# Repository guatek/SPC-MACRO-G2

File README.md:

# KiCAD Electronics for Gen 2 SPC-MACRO with Fluorescence Imaging

## Overview

This design is based on the first generation of the SPC-MACRO that used a system controller from the OriginalDesign/SPC-UW-MOD1 project and illumination from the OriginalDesign/SPCInterfaceBoard-SPCPWSSC/SPCInterfaceBoard-v01.kicad_pro project. The system control and power path are standard items that are in general common to most SPC microscopes. In contrast, the illumination is specific to the SPC-MACRO.

## Generation 2 changes

The G2 version is targeting fluorescence imaging and as such replaces the color darkfield ring illumination with Cree XE-G Violet ring illumination on both sides of the imaged volume. The system retains the small-angle color darkfield illumination used in the SPC-MACRO.

## Actions Items 

- Update the existing projects (SPCInterfaceBoard-v01.kicad_pro, and SPC-UW-MOD1.kicad_pcb) to work with KiCAD 7 (this is mostly done).
- Consolidate the upgrades from recent dual-mag projects and existing SPC-MACRO project to a single controller using either the SAMD21 or SAMD51. Functions of the dual-mag and SPC-MACRO should be retained. 
- Review and revise the illumination electronics and updated as needed to bring into parity with the latest dual-mag illumination.
- Update system controller and color darkfield illumination layout to fit in 4" ID form factor so boards can be used with dual-mag cameras.
- Add darkfield ring illumination with XE-G Violet LEDs packed as close as possible with Ledil 10 mm secondary optics.

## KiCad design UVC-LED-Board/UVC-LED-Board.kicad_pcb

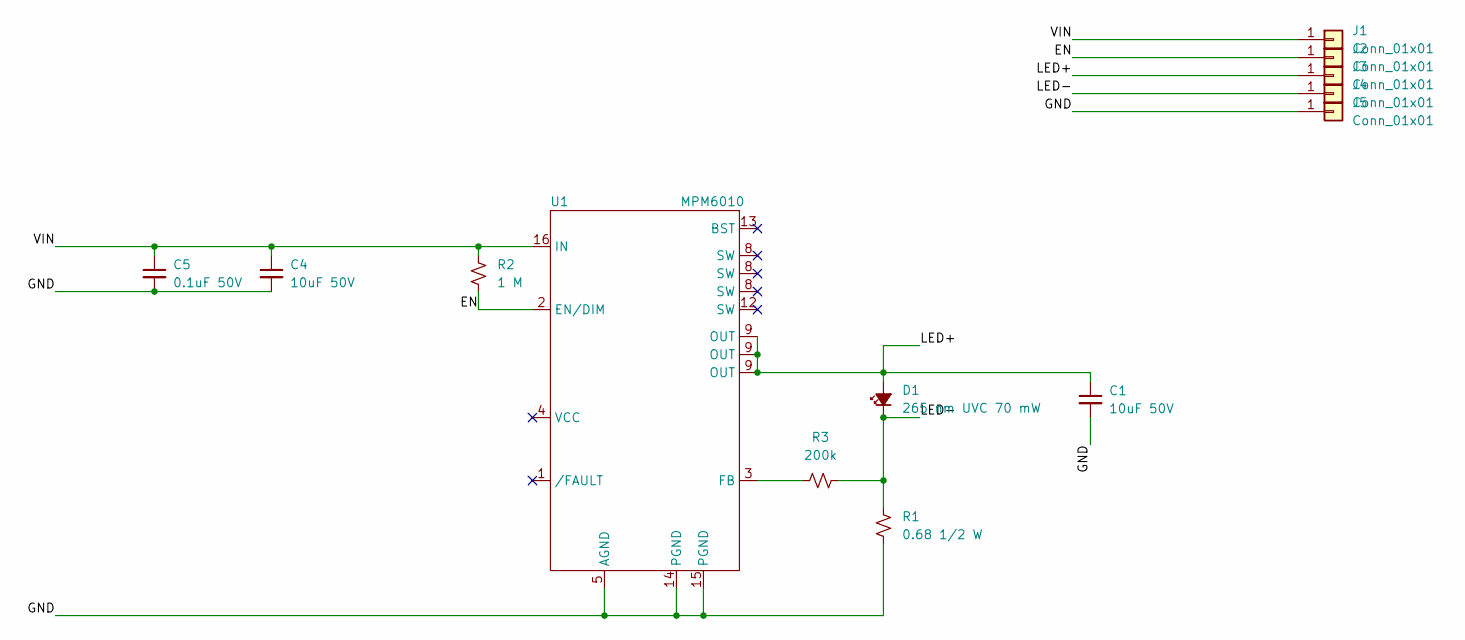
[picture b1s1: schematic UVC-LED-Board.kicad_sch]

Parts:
C1, C4: 10uF 50V; C_0805_2012Metric; Part Number 2571-GMC21X5R106K50NTTR-ND
C5: 0.1uF 50V; C_0402_1005Metric; Part Number 490-14514-1-ND
D1: 265 nm UVC 70 mW; ZEUBE265-1DA
J1, J2, J3, J4, J5: Conn_01x01; One_PTH
R1: 0.68 1/2 W; R_0805_2012Metric; Part Number P19304CT-ND
R2: 1 M; R_0402_1005Metric; Part Number P1.00MLCT-ND
R3: 200k; R_0402_1005Metric; Part Number P200KLCT-ND
U1: MPM6010; Part Number 1589-1774-1-ND

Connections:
/EN: J2.1, R2.2, U1.2 (EN/DIM)
/GND: C1.2, C4.2, C5.2, J5.1, R1.2, U1.5 (AGND), U1.14 (PGND), U1.15 (PGND)
/LED+: C1.1, D1.2 (A), J3.1, U1.9 (OUT)
/LED-: D1.1 (K), J4.1, R1.1, R3.2
/VIN: C4.1, C5.1, J1.1, R2.1, U1.16 (IN)
unnamed: R3.1, U1.3 (FB)

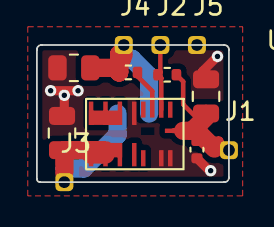
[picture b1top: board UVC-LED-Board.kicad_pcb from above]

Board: 4 copper layers, 10.7 x 7.6 mm, 13 parts (1 on the bottom side), 6 nets.

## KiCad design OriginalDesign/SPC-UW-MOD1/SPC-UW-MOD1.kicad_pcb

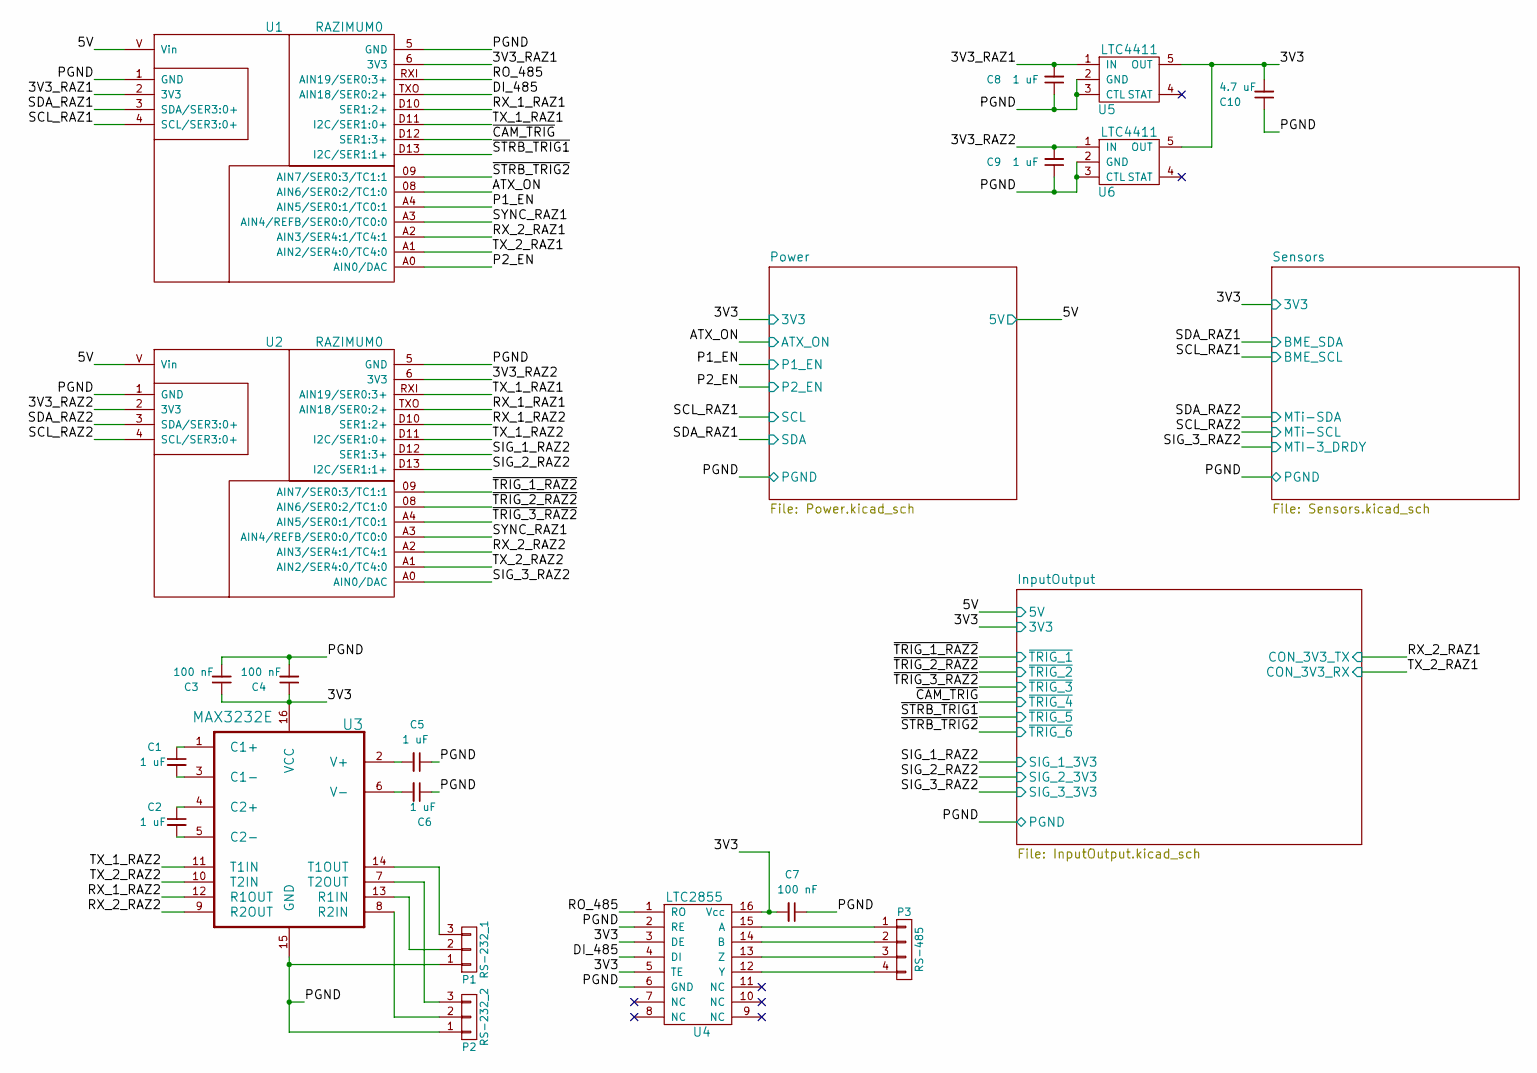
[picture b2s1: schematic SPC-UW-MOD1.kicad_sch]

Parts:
C1, C2, C5, C6: 1 uF; C_0805; Part Number UMK212B7105KG-T
C3, C4, C7: 100 nF; C_0603; Part Number GRM188R71H104KA93D
C8, C9: 1 uF; C_0603; Part Number C1608X7R1A105K080AC
C10: 4.7 uF; C_0805; Part Number GRM21BR71A475KA73K
P1: RS-232_1; Molex_NanoFit_2x02x2.50mm_Angled
P2: RS-232_2; Molex_NanoFit_2x02x2.50mm_Angled
P3: RS-485; Molex_NanoFit_2x02x2.50mm_Angled
U1, U2: RAZIMUM0
U3: MAX3232E; TSSOP-16_4.4x5mm_Pitch0.65mm; Part Number MAX3232ECUE+T
U4: LTC2855; SSOP-16_3.9x4.9mm_Pitch0.635mm; Part Number LTC2855IGN#PBF
U5, U6: LTC4411; TSOT-23-5

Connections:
/3V3_RAZ1: C8.2, U1.2 (3V3), U1.6 (3V3), U5.1 (IN)
/3V3_RAZ2: C9.2, U2.2 (3V3), U2.6 (3V3), U6.1 (IN)
/5V: U1.V (Vin), U2.V (Vin); also elsewhere on the board
/ATX_ON: U1.08 (AIN6/SER0:2/TC1:0); also elsewhere on the board
/DI_485: U1.TXO (AIN18/SER0:2+), U4.4 (DI)
/P1_EN: U1.A4 (AIN5/SER0:1/TC0:1); also elsewhere on the board
/P2_EN: U1.A0 (AIN0/DAC); also elsewhere on the board
/PGND: C3.2, C4.2, C5.1, C6.1, C7.1, C8.1, C9.1, C10.1, P1.1, P2.1, U1.1 (GND), U1.5 (GND), U2.1 (GND), U2.5 (GND), U3.15 (GND), U4.2 (RE), U4.6 (GND), U5.2 (GND), U5.3 (CTL), U6.2 (GND), U6.3 (CTL); also elsewhere on the board
/RO_485: U1.RXI (AIN19/SER0:3+), U4.1 (RO)
/RX_1_RAZ1: U1.D10 (SER1:2+), U2.TXO (AIN18/SER0:2+)
/RX_1_RAZ2: U2.D10 (SER1:2+), U3.12 (R1OUT)
/RX_2_RAZ1: U1.A2 (AIN3/SER4:1/TC4:1); also elsewhere on the board
/RX_2_RAZ2: U2.A2 (AIN3/SER4:1/TC4:1), U3.9 (R2OUT)
/SCL_RAZ1: U1.4 (SCL/SER3:0+); also elsewhere on the board
/SCL_RAZ2: U2.4 (SCL/SER3:0+); also elsewhere on the board
/SDA_RAZ1: U1.3 (SDA/SER3:0+); also elsewhere on the board
/SDA_RAZ2: U2.3 (SDA/SER3:0+); also elsewhere on the board
/SIG_1_RAZ2: U2.D12 (SER1:3+); also elsewhere on the board
/SIG_2_RAZ2: U2.D13 (I2C/SER1:1+); also elsewhere on the board
/SIG_3_RAZ2: U2.A0 (AIN0/DAC); also elsewhere on the board
/SYNC_RAZ1: U1.A3 (AIN4/REFB/SER0:0/TC0:0), U2.A3 (AIN4/REFB/SER0:0/TC0:0)
/TX_1_RAZ1: U1.D11 (I2C/SER1:0+), U2.RXI (AIN19/SER0:3+)
/TX_1_RAZ2: U2.D11 (I2C/SER1:0+), U3.11 (T1IN)
/TX_2_RAZ1: U1.A1 (AIN2/SER4:0/TC4:0); also elsewhere on the board
/TX_2_RAZ2: U2.A1 (AIN2/SER4:0/TC4:0), U3.10 (T2IN)
/~CAM_TRIG: U1.D12 (SER1:3+); also elsewhere on the board
/~STRB_TRIG1: U1.D13 (I2C/SER1:1+); also elsewhere on the board
/~STRB_TRIG2: U1.09 (AIN7/SER0:3/TC1:1); also elsewhere on the board
/~TRIG_1_RAZ2: U2.09 (AIN7/SER0:3/TC1:1); also elsewhere on the board
/~TRIG_2_RAZ2: U2.08 (AIN6/SER0:2/TC1:0); also elsewhere on the board
/~TRIG_3_RAZ2: U2.A4 (AIN5/SER0:1/TC0:1); also elsewhere on the board
unnamed: C1.1, U3.1 (C1+)
unnamed: C1.2, U3.3 (C1-)
unnamed: C2.1, U3.4 (C2+)
unnamed: C2.2, U3.5 (C2-)
unnamed: C5.2, U3.2 (V+)
unnamed: C6.2, U3.6 (V-)
unnamed: P1.2, U3.13 (R1IN)
unnamed: P1.3, U3.14 (T1OUT)
unnamed: P2.2, U3.8 (R2IN)
unnamed: P2.3, U3.7 (T2OUT)
unnamed: P3.1, U4.15 (A)
unnamed: P3.2, U4.14 (B)
unnamed: P3.3, U4.13 (Z)
unnamed: P3.4, U4.12 (Y)

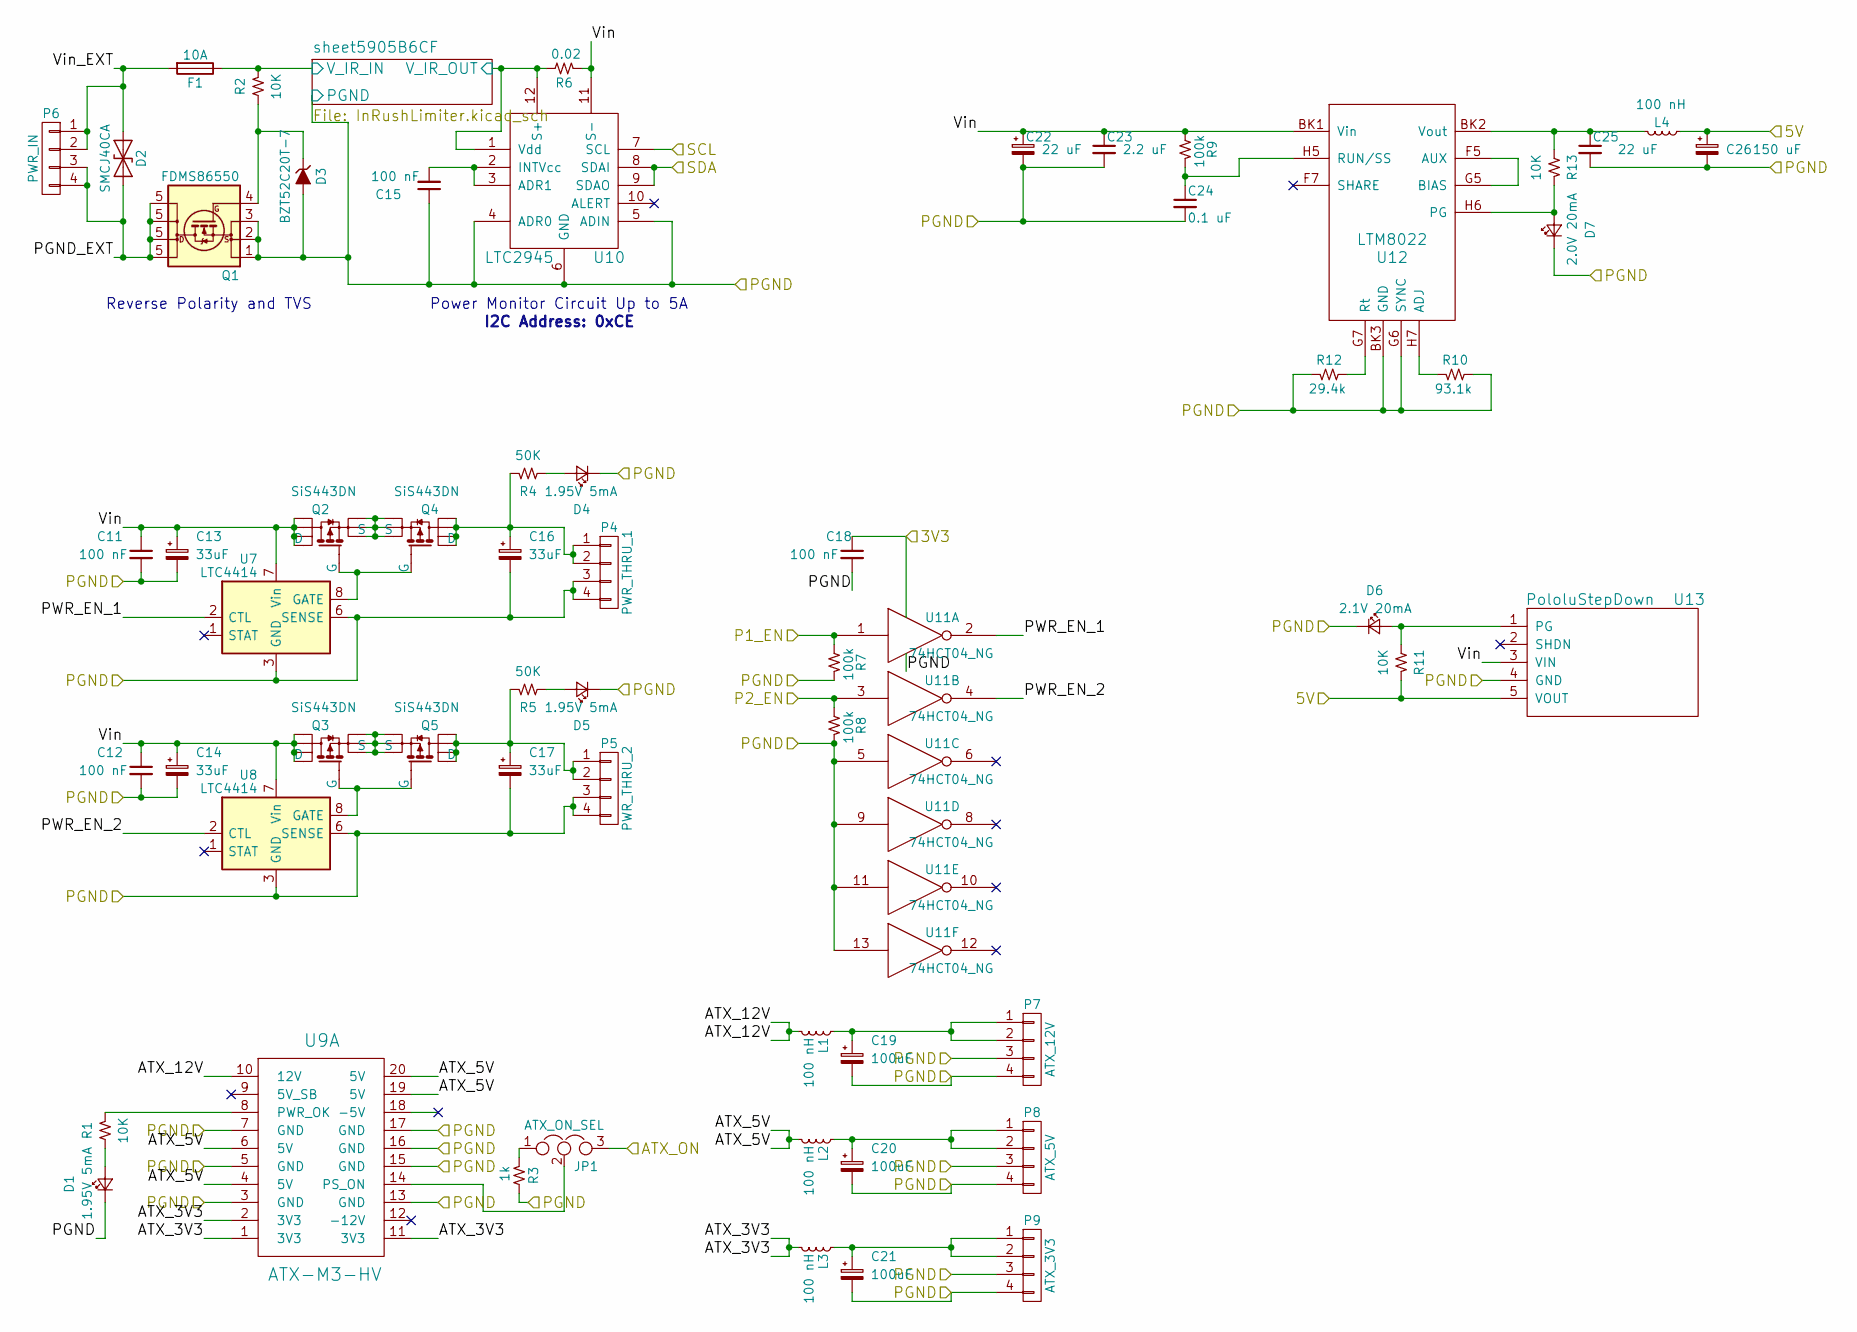
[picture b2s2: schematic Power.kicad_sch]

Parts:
C11, C12, C15, C18: 100 nF; C_0603; Part Number GRM188R71H104KA93D
C13, C14, C16, C17: 33uF; CP_Tantalum_Case-V_EIA-7343-20_Reflow; Part Number T521X336M050ATE075
C19, C20, C21: 100uF; CP_Tantalum_Case-V_EIA-7343-20_Reflow; Part Number TCJE107M025R0080
C22: 22 uF; CP_Elec_6.3x5.3
C23: 2.2 uF; C_1206; Part Number C1206C225J5RAC7800
C24: 0.1 uF; C_0603
C25: 22 uF; C_1210
C26: 150 uF; TantalC_SizeE_EIA-7360_Reflow; Part Number TCN4157M025R0070
D1, D4, D5: 1.95V 5mA; LED_0603; Part Number LNJ437W84RA
D2: SMCJ40CA; D_SMC_Standard; Part Number SMCJ40CA
D3: BZT52C20T-7; D_SOD-523; Part Number BZT52C20T-7
D6: 2.1V 20mA; LED_0603; Part Number LTST-C191KSKT
D7: 2.0V 20mA; LED_0603; Part Number ASMT-RF45-AN002
F1: 10A; Fuse_SMD; Part Number 01550900M
JP1: ATX_ON_SEL; JP-3Way-0402
L1, L2, L3, L4: 100 nH; IHLP2525CZERR10M01; Part Number IHLP2525CZERR10M01
P4: PWR_THRU_1; Molex_NanoFit_2x02x2.50mm_Angled
P5: PWR_THRU_2; Molex_NanoFit_2x02x2.50mm_Angled
P6: PWR_IN; Molex_NanoFit_2x02x2.50mm_Angled
P7: ATX_12V; Molex_NanoFit_2x02x2.50mm_Angled
P8: ATX_5V; Molex_NanoFit_2x02x2.50mm_Angled
P9: ATX_3V3; Molex_NanoFit_2x02x2.50mm_Angled
Q1: FDMS86550; TDSON-8-1; Part number FDMS86550
Q2, Q3, Q4, Q5: SiS443DN; Part Number SiS443DN
R1, R2, R11, R13: 10K; R_0603
R3: 1k; R_0603; Part Number RC0603FR-071KL
R4, R5: 50K; R_0603; Part Number RC0603JR-0751KL
R6: 0.02; R_2010; Part Number WSL2010R0200FEA18
R7, R8, R9: 100k; R_0603
R10: 93.1k; R_0603; Part Number ERA-3AEB9312V
R12: 29.4k; R_0603; Part Number ERA-3AEB2942V
U7, U8: LTC4414; MSOP-8_3x3mm_Pitch0.65mm
U9: ATX-M3-HV; Molex_MiniFit-JR-5569-20A2_2x10x4.20mm_Angled
U10: LTC2945; MSOP-12_3x4mm_Pitch0.65mm
U11: 74HCT04_NG
U12: LTM8022
U13: PololuStepDown; POLOLUBUCKREG_2p5A

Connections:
/5V: C26.1, L4.1, R11.1, U13.5 (VOUT); also elsewhere on the board
/ATX_ON: JP1.3; also elsewhere on the board
/P1_EN: R7.2, U11.1; also elsewhere on the board
/P2_EN: R8.2, U11.3; also elsewhere on the board
/PGND: C11.2, C12.2, C13.2, C14.2, C15.1, C16.2, C17.2, C18.2, C19.2, C20.2, C21.2, C22.2, C23.2, C24.2, C25.2, C26.2, D1.1 (K), D3.2 (A), D4.1 (K), D5.1 (K), D6.1 (K), D7.1 (K), P4.3, P4.4, P5.3, P5.4, P7.3, P7.4, P8.3, P8.4, P9.3, P9.4, Q1.1 (S), Q1.2 (S), Q1.3 (S), R3.2, R7.1, R8.1, R10.2, R12.1, U7.3 (GND), U7.6 (SENSE), U8.3 (GND), U8.6 (SENSE), U9.3 (GND), U9.5 (GND), U9.7 (GND), U9.13 (GND), U9.15 (GND), U9.16 (GND), U9.17 (GND), U10.4 (ADR0), U10.5 (ADIN), U10.6 (GND), U11.5, U11.7 (GND), U11.9, U11.11, U11.13, U12.BK3 (GND), U12.G6 (SYNC), U13.4 (GND); also elsewhere on the board
/Power/ATX_3V3: L3.2, U9.1 (3V3), U9.2 (3V3), U9.11 (3V3)
/Power/ATX_5V: L2.2, U9.4 (5V), U9.6 (5V), U9.19 (5V), U9.20 (5V)
/Power/ATX_12V: L1.2, U9.10 (12V)
/Power/PGND_EXT: D2.2 (A2), P6.3, P6.4, Q1.5 (D)
/Power/PWR_EN_1: U7.2 (CTL), U11.2
/Power/PWR_EN_2: U8.2 (CTL), U11.4
/Power/Vin: C11.1, C12.1, C13.1, C14.1, C22.1, C23.1, Q2.5 (D), Q2.6 (D), Q2.7 (D), Q2.8 (D), Q3.5 (D), Q3.6 (D), Q3.7 (D), Q3.8 (D), R6.1, R9.2, U7.7 (Vin), U8.7 (Vin), U10.11 (S-), U12.BK1 (Vin), U13.3 (VIN)
/Power/Vin_EXT: D2.1 (A1), F1.2, P6.1, P6.2
/Power/sheet5905B6CF/V_IR_IN: F1.1, R2.1; also elsewhere on the board
/Power/sheet5905B6CF/V_IR_OUT: R6.2, U10.1 (Vdd), U10.12 (S+); also elsewhere on the board
/SCL_RAZ1: U10.7 (SCL); also elsewhere on the board
/SDA_RAZ1: U10.8 (SDAI), U10.9 (SDAO); also elsewhere on the board
unnamed: C15.2, U10.2 (INTVcc), U10.3 (ADR1)
unnamed: C16.1, P4.1, P4.2, Q4.5 (D), Q4.6 (D), Q4.7 (D), Q4.8 (D), R4.1
unnamed: C17.1, P5.1, P5.2, Q5.5 (D), Q5.6 (D), Q5.7 (D), Q5.8 (D), R5.1
unnamed: C19.1, L1.1, P7.1, P7.2
unnamed: C20.1, L2.1, P8.1, P8.2
unnamed: C21.1, L3.1, P9.1, P9.2
unnamed: C24.1, R9.1, U12.H5 (RUN/SS)
unnamed: C25.1, L4.2, R13.2, U12.BK2 (Vout)
unnamed: D1.2 (A), R1.2
unnamed: D3.1 (K), Q1.4 (G), R2.2
unnamed: D4.2 (A), R4.2
unnamed: D5.2 (A), R5.2
unnamed: D6.2 (A), R11.2, U13.1 (PG)
unnamed: D7.2 (A), R13.1, U12.H6 (PG)
unnamed: JP1.1, R3.1
unnamed: JP1.2, U9.14 (PS_ON)
unnamed: Q2.1 (S), Q2.2 (S), Q2.3 (S), Q4.1 (S), Q4.2 (S), Q4.3 (S)
unnamed: Q2.4 (G), Q4.4 (G), U7.8 (GATE)
unnamed: Q3.1 (S), Q3.2 (S), Q3.3 (S), Q5.1 (S), Q5.2 (S), Q5.3 (S)
unnamed: Q3.4 (G), Q5.4 (G), U8.8 (GATE)
unnamed: R1.1, U9.8 (PWR_OK)
unnamed: R10.1, U12.H7 (ADJ)
unnamed: R12.2, U12.G7 (Rt)
unnamed: U12.F5 (AUX), U12.G5 (BIAS)

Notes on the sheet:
Power Monitor Circuit Up to 5A
I2C Address: 0xCE
Reverse Polarity and TVS

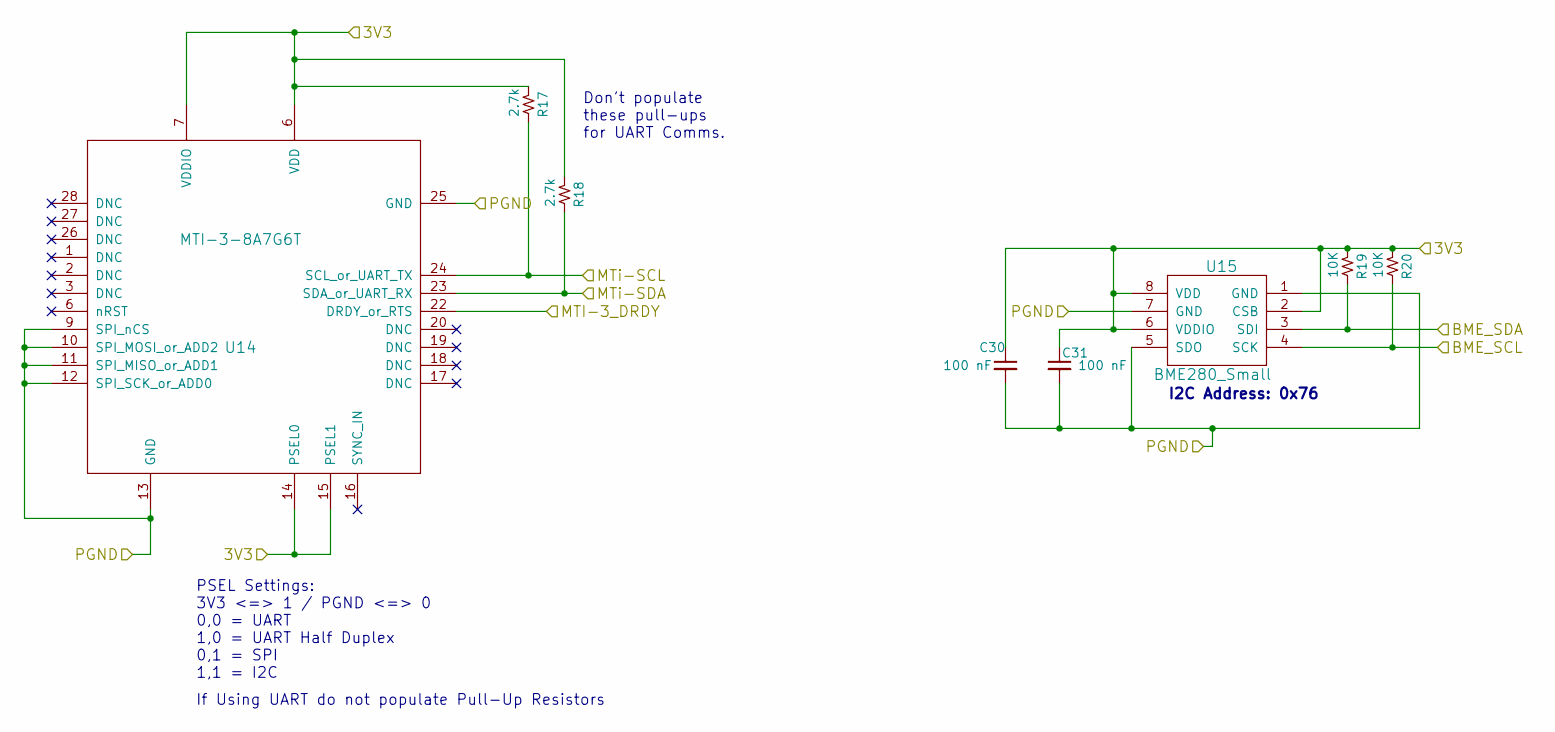
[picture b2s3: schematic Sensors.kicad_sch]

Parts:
C30, C31: 100 nF; C_0603; Part Number GRM188R71H104KA93D
R17, R18: 2.7k; R_0603; Part Number CRCW06032K70FKEAHP
R19, R20: 10K; R_0603
U14: MTI-3-8A7G6T; PLCC28
U15: BME280_Small; BME280

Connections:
/PGND: C30.2, C31.2, U14.9 (SPI_nCS), U14.10 (SPI_MOSI_or_ADD2), U14.11 (SPI_MISO_or_ADD1), U14.12 (SPI_SCK_or_ADD0), U14.13 (GND), U14.25 (GND), U15.1 (GND), U15.5 (SDO), U15.7 (GND); also elsewhere on the board
/SCL_RAZ1: R20.2, U15.4 (SCK); also elsewhere on the board
/SCL_RAZ2: R17.2, U14.24 (SCL_or_UART_TX); also elsewhere on the board
/SDA_RAZ1: R19.2, U15.3 (SDI); also elsewhere on the board
/SDA_RAZ2: R18.2, U14.23 (SDA_or_UART_RX); also elsewhere on the board
/SIG_3_RAZ2: U14.22 (DRDY_or_RTS); also elsewhere on the board

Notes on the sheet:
If Using UART do not populate Pull-Up Resistors
I2C Address: 0x76
Don't populate these pull-ups for UART Comms.
PSEL Settings: 3V3 <=> 1 / PGND <=> 0 0,0 = UART 1,0 = UART Half Duplex 0,1 = SPI 1,1 = I2C

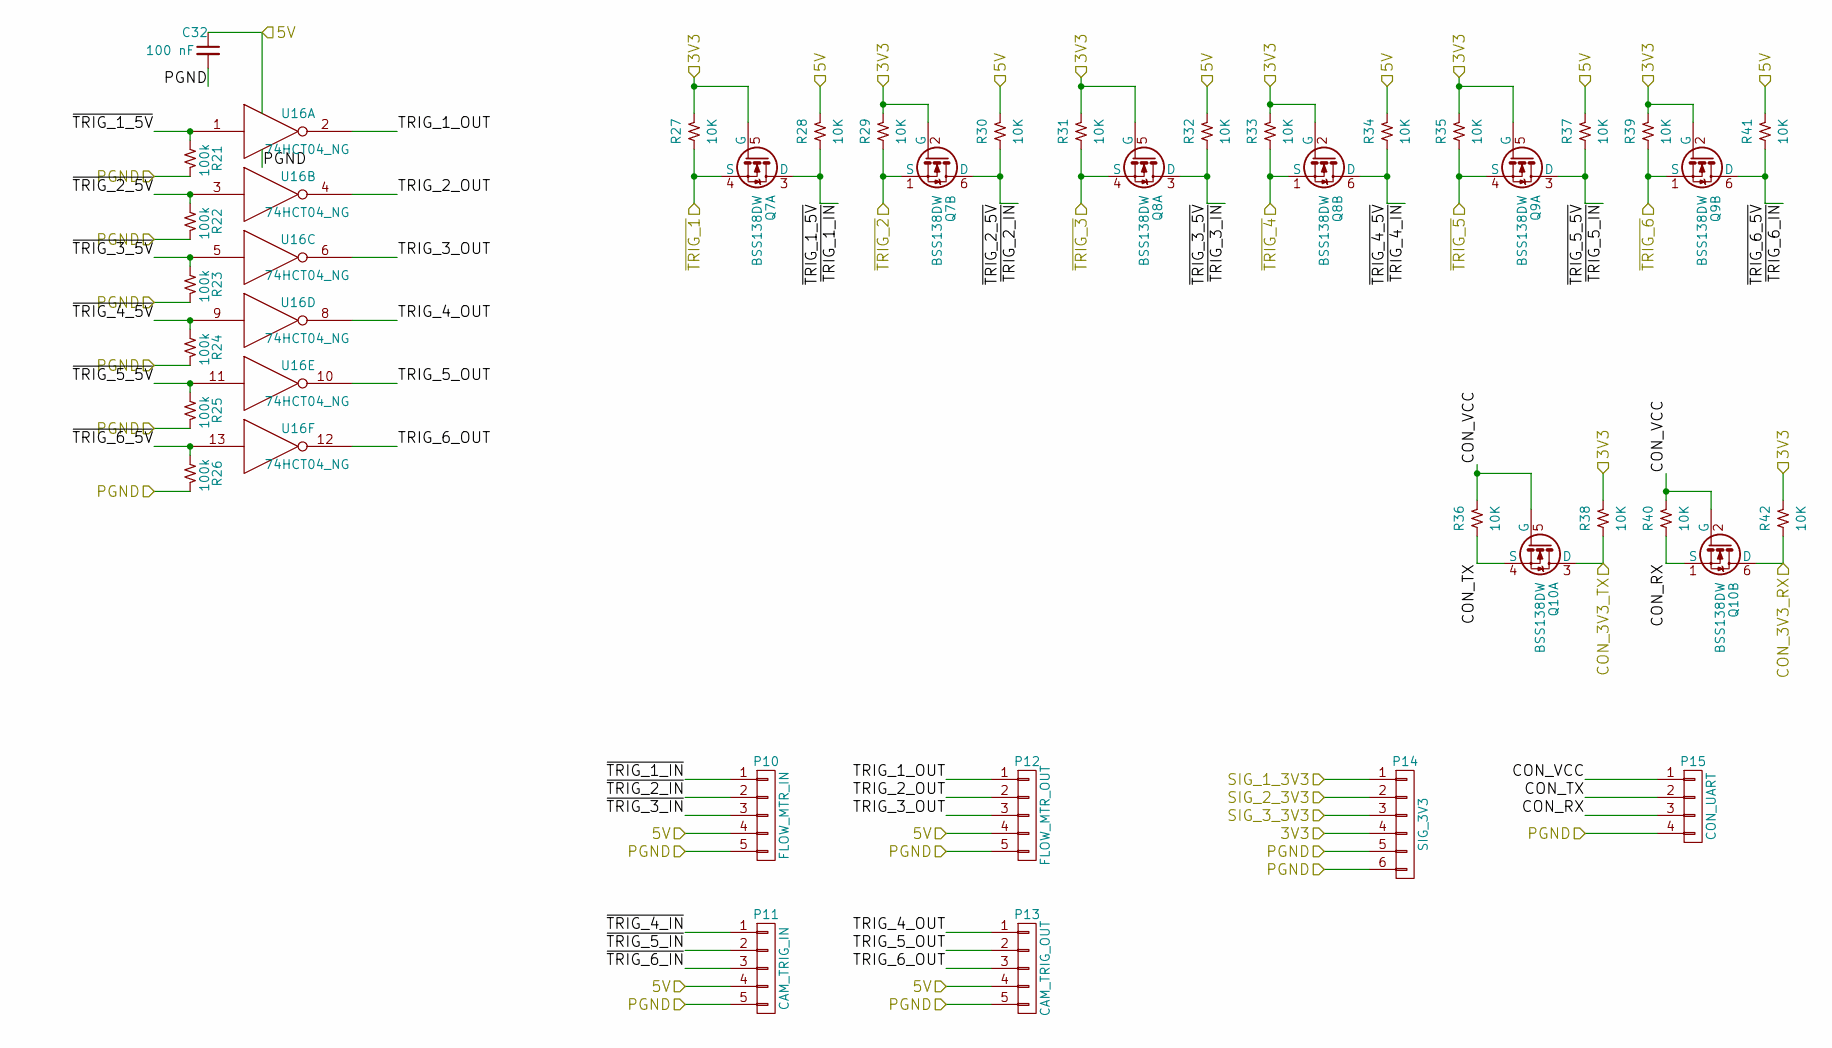
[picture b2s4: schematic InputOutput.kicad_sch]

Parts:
C32: 100 nF; C_0603; Part Number GRM188R71H104KA93D
P10: FLOW_MTR_IN; Molex_NanoFit_2x03x2.50mm_Angled
P11: CAM_TRIG_IN; Molex_NanoFit_2x03x2.50mm_Angled
P12: FLOW_MTR_OUT; Molex_NanoFit_2x03x2.50mm_Angled
P13: CAM_TRIG_OUT; Molex_NanoFit_2x03x2.50mm_Angled
P14: SIG_3V3; Molex_NanoFit_2x03x2.50mm_Angled
P15: CON_UART; Molex_NanoFit_2x02x2.50mm_Angled
Q7, Q8, Q9, Q10: BSS138DW; SOT-363_SC-70-6
R21, R22, R23, R24, R25, R26: 100k; R_0603
R27, R28, R29, R30, R31, R32, R33, R34, R35, R36, R37, R38, R39, R40, R41, R42: 10K; R_0603
U16: 74HCT04_NG

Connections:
/5V: C32.1, P10.4, P11.4, P12.4, P13.4, R28.1, R30.1, R32.1, R34.1, R37.1, R41.1, U16.14 (VCC); also elsewhere on the board
/InputOutput/CON_RX: P15.3, Q10.1 (S), R40.2
/InputOutput/CON_TX: P15.2, Q10.4 (S), R36.2
/InputOutput/CON_VCC: P15.1, Q10.2 (G), Q10.5 (G), R36.1, R40.1
/InputOutput/TRIG_1_OUT: P12.1, U16.2
/InputOutput/TRIG_2_OUT: P12.2, U16.4
/InputOutput/TRIG_3_OUT: P12.3, U16.6
/InputOutput/TRIG_4_OUT: P13.1, U16.8
/InputOutput/TRIG_5_OUT: P13.2, U16.10
/InputOutput/TRIG_6_OUT: P13.3, U16.12
/InputOutput/~TRIG_1_5V: P10.1, Q7.3 (D), R21.2, R28.2, U16.1
/InputOutput/~TRIG_2_5V: P10.2, Q7.6 (D), R22.2, R30.2, U16.3
/InputOutput/~TRIG_3_5V: P10.3, Q8.3 (D), R23.2, R32.2, U16.5
/InputOutput/~TRIG_4_5V: P11.1, Q8.6 (D), R24.2, R34.2, U16.9
/InputOutput/~TRIG_5_5V: P11.2, Q9.3 (D), R25.2, R37.2, U16.11
/InputOutput/~TRIG_6_5V: P11.3, Q9.6 (D), R26.2, R41.2, U16.13
/PGND: C32.2, P10.5, P11.5, P12.5, P13.5, P14.5, P14.6, P15.4, R21.1, R22.1, R23.1, R24.1, R25.1, R26.1, U16.7 (GND); also elsewhere on the board
/RX_2_RAZ1: Q10.3 (D), R38.2; also elsewhere on the board
/SIG_1_RAZ2: P14.1; also elsewhere on the board
/SIG_2_RAZ2: P14.2; also elsewhere on the board
/SIG_3_RAZ2: P14.3; also elsewhere on the board
/TX_2_RAZ1: Q10.6 (D), R42.2; also elsewhere on the board
/~CAM_TRIG: Q8.1 (S), R33.2; also elsewhere on the board
/~STRB_TRIG1: Q9.4 (S), R35.2; also elsewhere on the board
/~STRB_TRIG2: Q9.1 (S), R39.2; also elsewhere on the board
/~TRIG_1_RAZ2: Q7.4 (S), R27.2; also elsewhere on the board
/~TRIG_2_RAZ2: Q7.1 (S), R29.2; also elsewhere on the board
/~TRIG_3_RAZ2: Q8.4 (S), R31.2; also elsewhere on the board

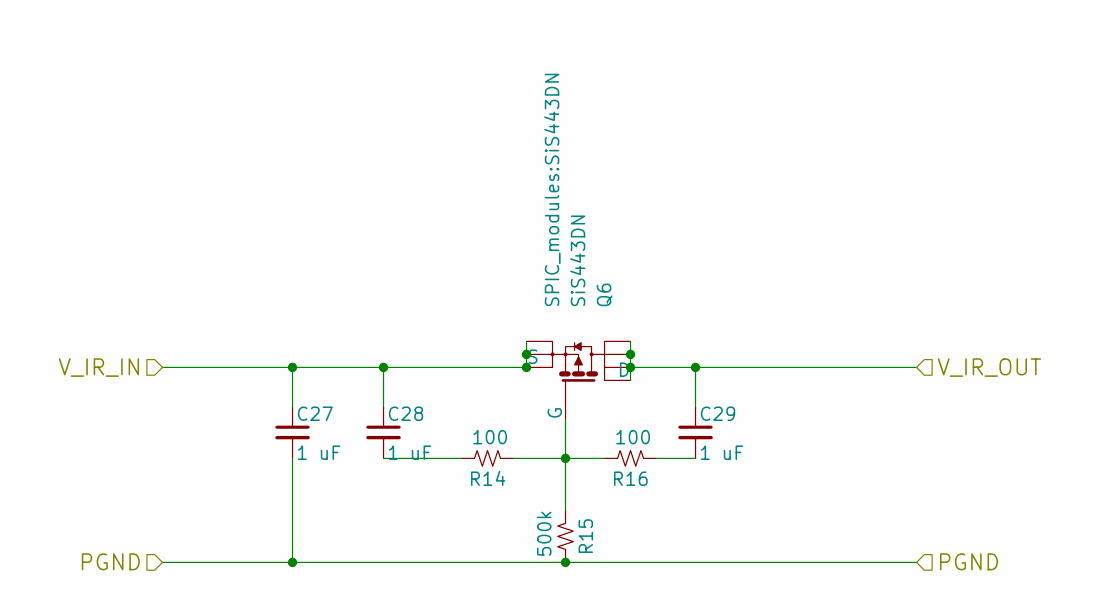
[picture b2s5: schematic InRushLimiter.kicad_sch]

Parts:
C27, C28, C29: 1 uF; C_0805; Part Number UMK212B7105KG-T
Q6: SiS443DN
R14, R16: 100; R_0805; Part Number RC0805FR-07100RL
R15: 500k; R_0805; Part Number RC0805FR-07499KL

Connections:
/PGND: C27.2, R15.2; also elsewhere on the board
/Power/sheet5905B6CF/V_IR_IN: C27.1, C28.1, Q6.1 (S), Q6.2 (S), Q6.3 (S); also elsewhere on the board
/Power/sheet5905B6CF/V_IR_OUT: C29.1, Q6.5 (D), Q6.6 (D), Q6.7 (D), Q6.8 (D); also elsewhere on the board
unnamed: C28.2, R14.2
unnamed: C29.2, R16.1
unnamed: Q6.4 (G), R14.1, R15.1, R16.2

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
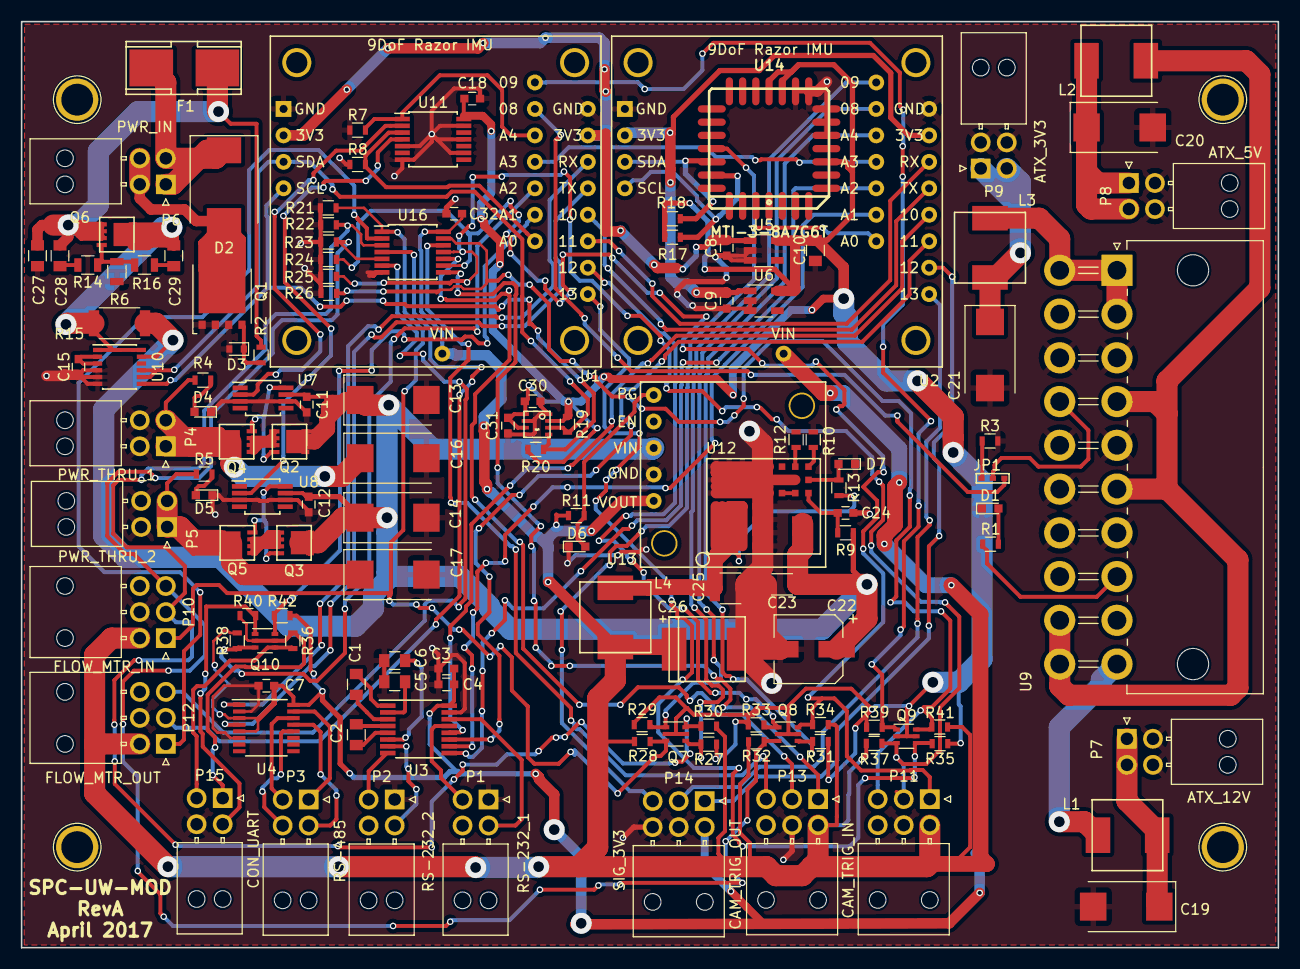
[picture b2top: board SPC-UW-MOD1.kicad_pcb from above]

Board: 2 copper layers, 120.7 x 88.9 mm, 128 parts (0 on the bottom side), 98 nets.

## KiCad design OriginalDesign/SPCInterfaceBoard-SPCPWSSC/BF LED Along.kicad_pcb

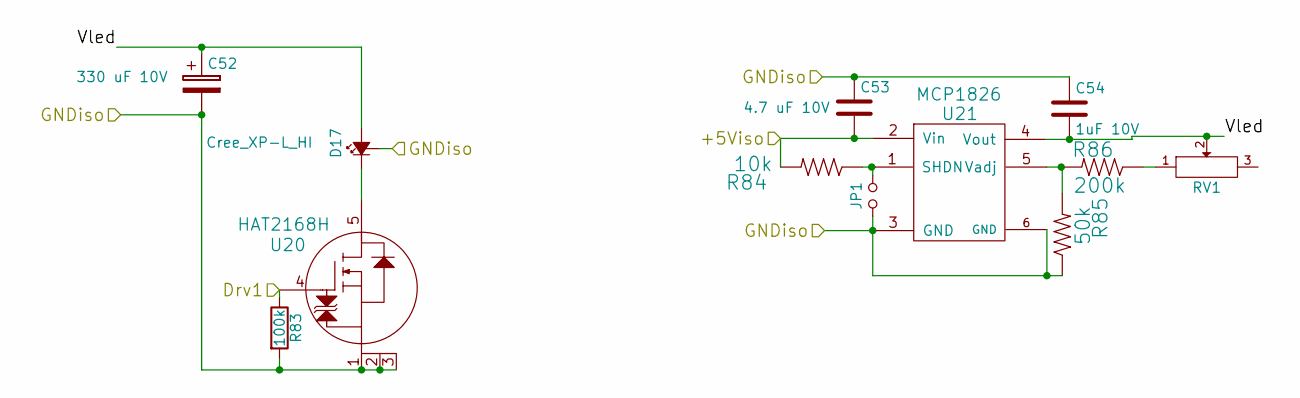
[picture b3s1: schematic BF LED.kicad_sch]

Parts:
C52: 330 uF 10V; TantalC_SizeD_EIA-7343_Reflow
C53: 4.7 uF 10V; c_0603
C54: 1uF 10V; c_0603
D17: Cree_XP-L_HI; Cree_XP-L_HI-vias-4
JP1: Jumper_NO_Small; R_0402
R83: 100k; r_0603
R84: 10k; r_0603
R85: 50k; r_0603
R86: 200k; r_0603
RV1: POT 250k; BOURNS3361P
U20: HAT2168H; SOT-669_LFPAK-vias
U21: MCP1826; d-pak-5

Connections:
/LED-DC-DC/BF LED/+5Viso: C53.2, R84.2, U21.2 (Vin); also elsewhere on the board
/LED-DC-DC/BF LED/Drv1: R83.1, U20.4; also elsewhere on the board
/LED-DC-DC/BF LED/Vled: C52.1, C54.2, D17.2 (A), RV1.2, U21.4 (Vout)
unnamed: D17.1 (K), U20.5
unnamed: JP1.2, R84.1, U21.1 (SHDN)
unnamed: R85.2, R86.2, U21.5 (Vadj)
unnamed: R86.1, RV1.1

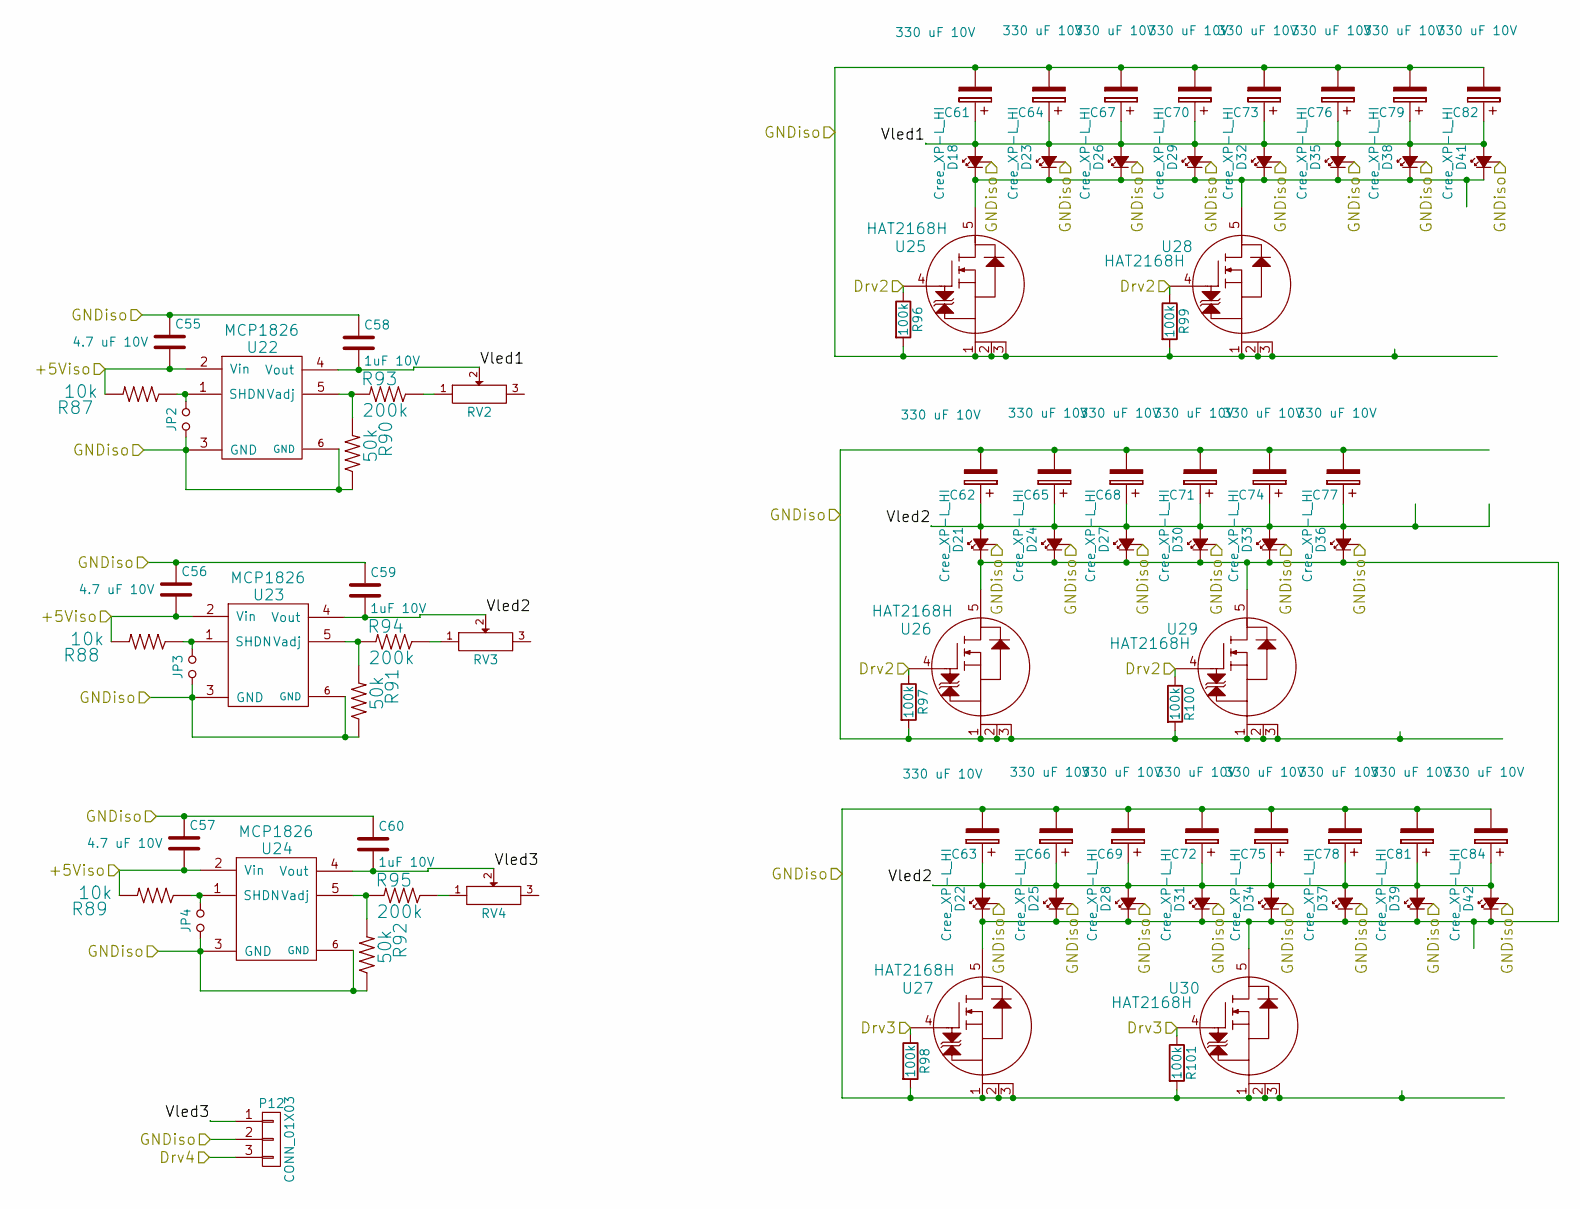
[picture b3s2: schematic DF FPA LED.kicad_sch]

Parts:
C55, C56, C57: 4.7 uF 10V; c_0603
C58, C59, C60: 1uF 10V; c_0603
C61, C62, C63, C64, C65, C66, C67, C68, C69, C70, C71, C72, C73, C74, C75, C76, C77, C78, C79, C81, C82, C84: 330 uF 10V; TantalC_SizeD_EIA-7343_Reflow
D18, D21, D22, D23, D24, D25, D26, D27, D28, D29, D30, D31, D32, D33, D34, D35, D36, D37, D38, D39, D41, D42: Cree_XP-L_HI; Cree_XP-L_HI-vias-4
JP2, JP3, JP4: Jumper_NO_Small; R_0402
P12: CONN_01X03; mpt_0,5%2f3-2,54
R87, R88, R89: 10k; r_0603
R90, R91, R92: 50k; r_0603
R93, R94, R95: 200k; r_0603
R96, R97, R98, R99, R100, R101: 100k; r_0603
RV2, RV3, RV4: POT 250k; BOURNS3361P
U22, U23, U24: MCP1826; d-pak-5
U25, U26, U27, U28, U29, U30: HAT2168H; SOT-669_LFPAK-vias

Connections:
/LED-DC-DC/BF LED/+5Viso: C55.2, C56.2, C57.2, R87.2, R88.2, R89.2, U22.2 (Vin), U23.2 (Vin), U24.2 (Vin); also elsewhere on the board
/LED-DC-DC/DF PFA LED/Drv2: R96.1, R97.1, R99.1, R100.1, U25.4, U26.4, U28.4, U29.4; also elsewhere on the board
/LED-DC-DC/DF PFA LED/Drv3: R98.1, R101.1, U27.4, U30.4; also elsewhere on the board
/LED-DC-DC/DF PFA LED/Drv4: P12.3; also elsewhere on the board
/LED-DC-DC/DF PFA LED/Vled1: C58.2, C61.1, C64.1, C67.1, C70.1, C73.1, C76.1, C79.1, C82.1, D18.2 (A), D23.2 (A), D26.2 (A), D29.2 (A), D32.2 (A), D35.2 (A), D38.2 (A), D41.2 (A), RV2.2, U22.4 (Vout)
/LED-DC-DC/DF PFA LED/Vled2: C59.2, C62.1, C63.1, C65.1, C66.1, C68.1, C69.1, C71.1, C72.1, C74.1, C75.1, C77.1, C78.1, C81.1, C84.1, D21.2 (A), D22.2 (A), D24.2 (A), D25.2 (A), D27.2 (A), D28.2 (A), D30.2 (A), D31.2 (A), D33.2 (A), D34.2 (A), D36.2 (A), D37.2 (A), D39.2 (A), D42.2 (A), RV3.2, U23.4 (Vout)
/LED-DC-DC/DF PFA LED/Vled3: C60.2, P12.1, RV4.2, U24.4 (Vout)
unnamed: D18.1 (K), D23.1 (K), D26.1 (K), D29.1 (K), D32.1 (K), D35.1 (K), D38.1 (K), D41.1 (K), U25.5, U28.5
unnamed: D21.1 (K), D22.1 (K), D24.1 (K), D25.1 (K), D27.1 (K), D28.1 (K), D30.1 (K), D31.1 (K), D33.1 (K), D34.1 (K), D36.1 (K), D37.1 (K), D39.1 (K), D42.1 (K), U26.5, U27.5, U29.5, U30.5
unnamed: JP2.2, R87.1, U22.1 (SHDN)
unnamed: JP3.2, R88.1, U23.1 (SHDN)
unnamed: JP4.2, R89.1, U24.1 (SHDN)
unnamed: R90.2, R93.2, U22.5 (Vadj)
unnamed: R91.2, R94.2, U23.5 (Vadj)
unnamed: R92.2, R95.2, U24.5 (Vadj)
unnamed: R93.1, RV2.1
unnamed: R94.1, RV3.1
unnamed: R95.1, RV4.1
